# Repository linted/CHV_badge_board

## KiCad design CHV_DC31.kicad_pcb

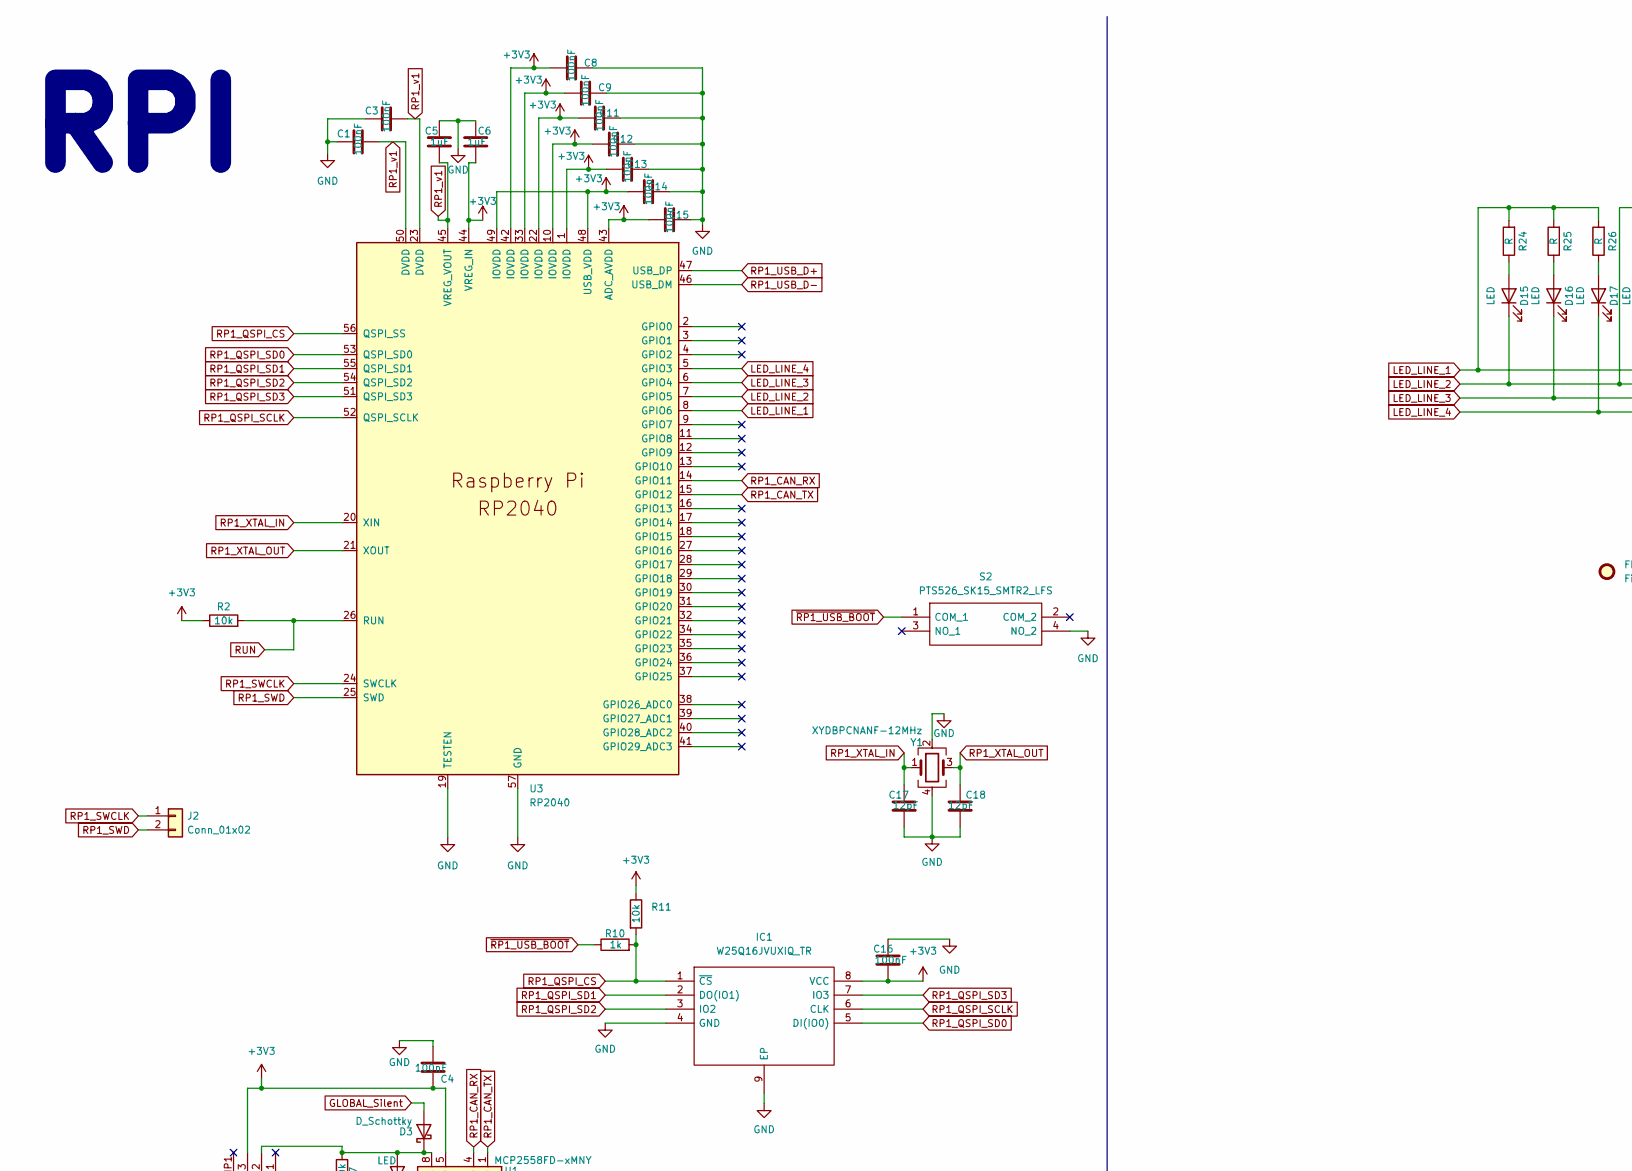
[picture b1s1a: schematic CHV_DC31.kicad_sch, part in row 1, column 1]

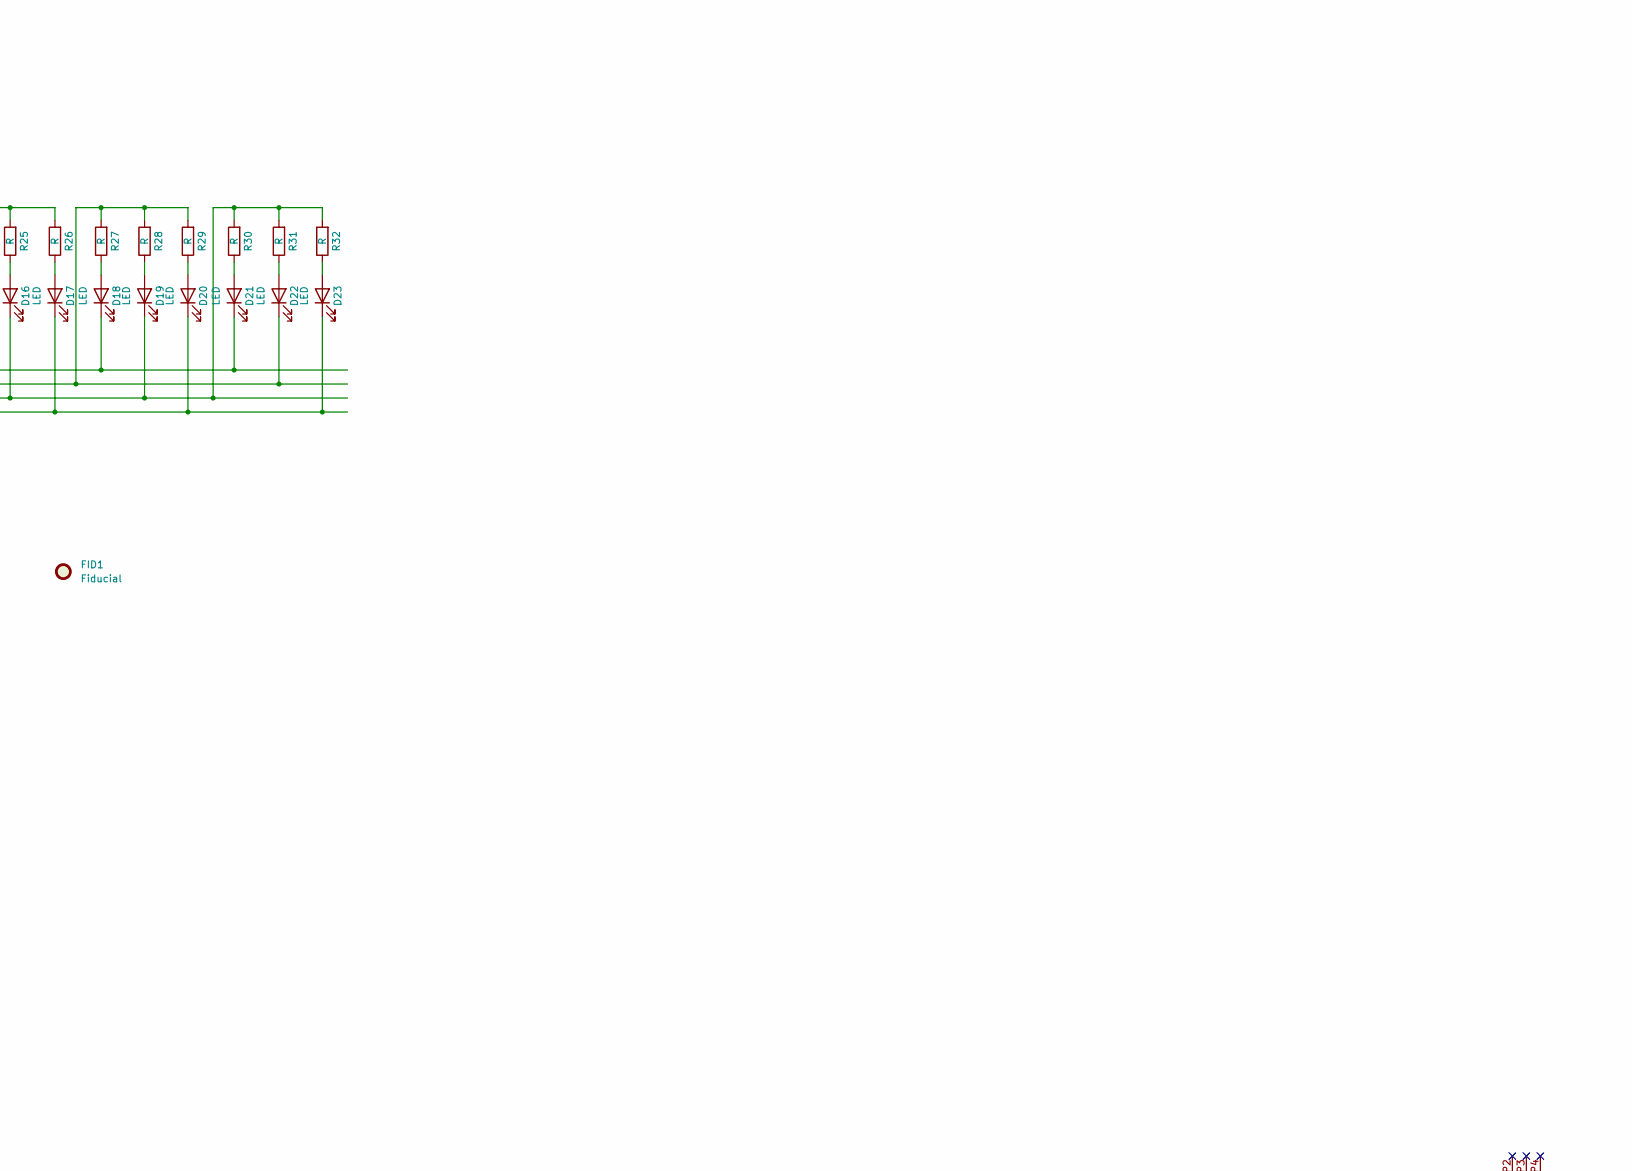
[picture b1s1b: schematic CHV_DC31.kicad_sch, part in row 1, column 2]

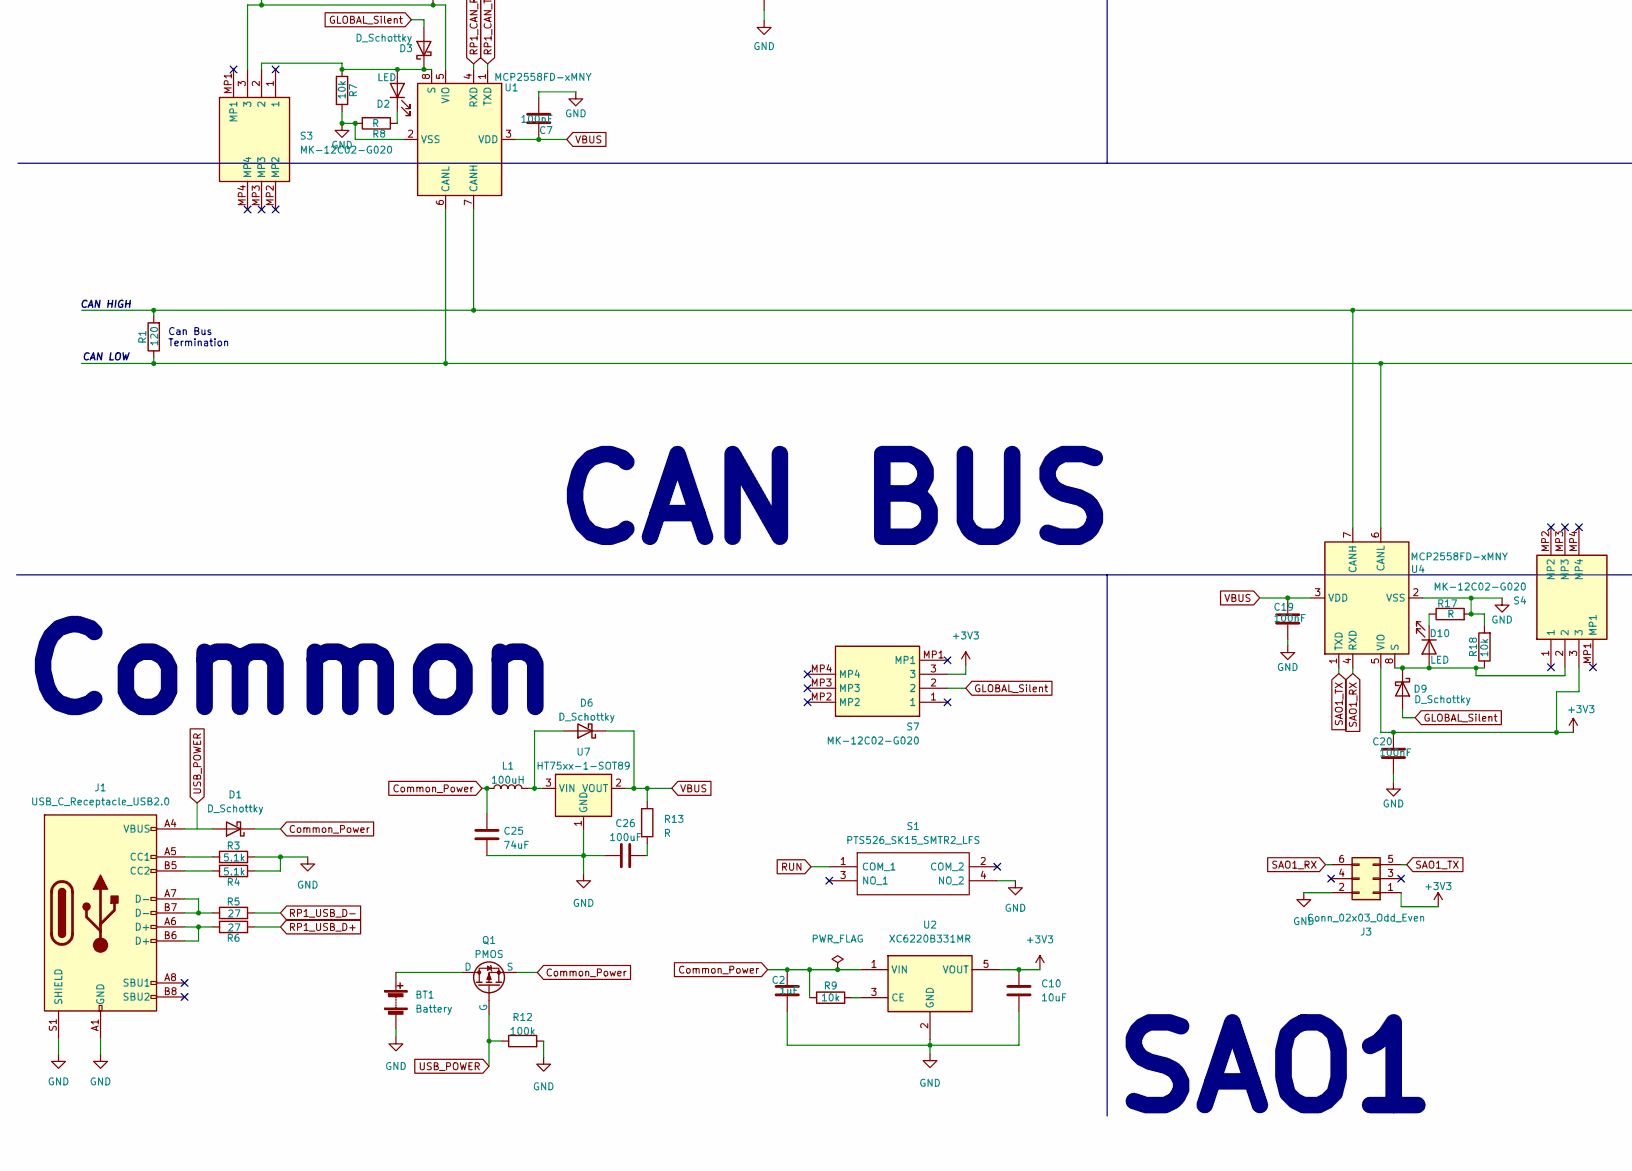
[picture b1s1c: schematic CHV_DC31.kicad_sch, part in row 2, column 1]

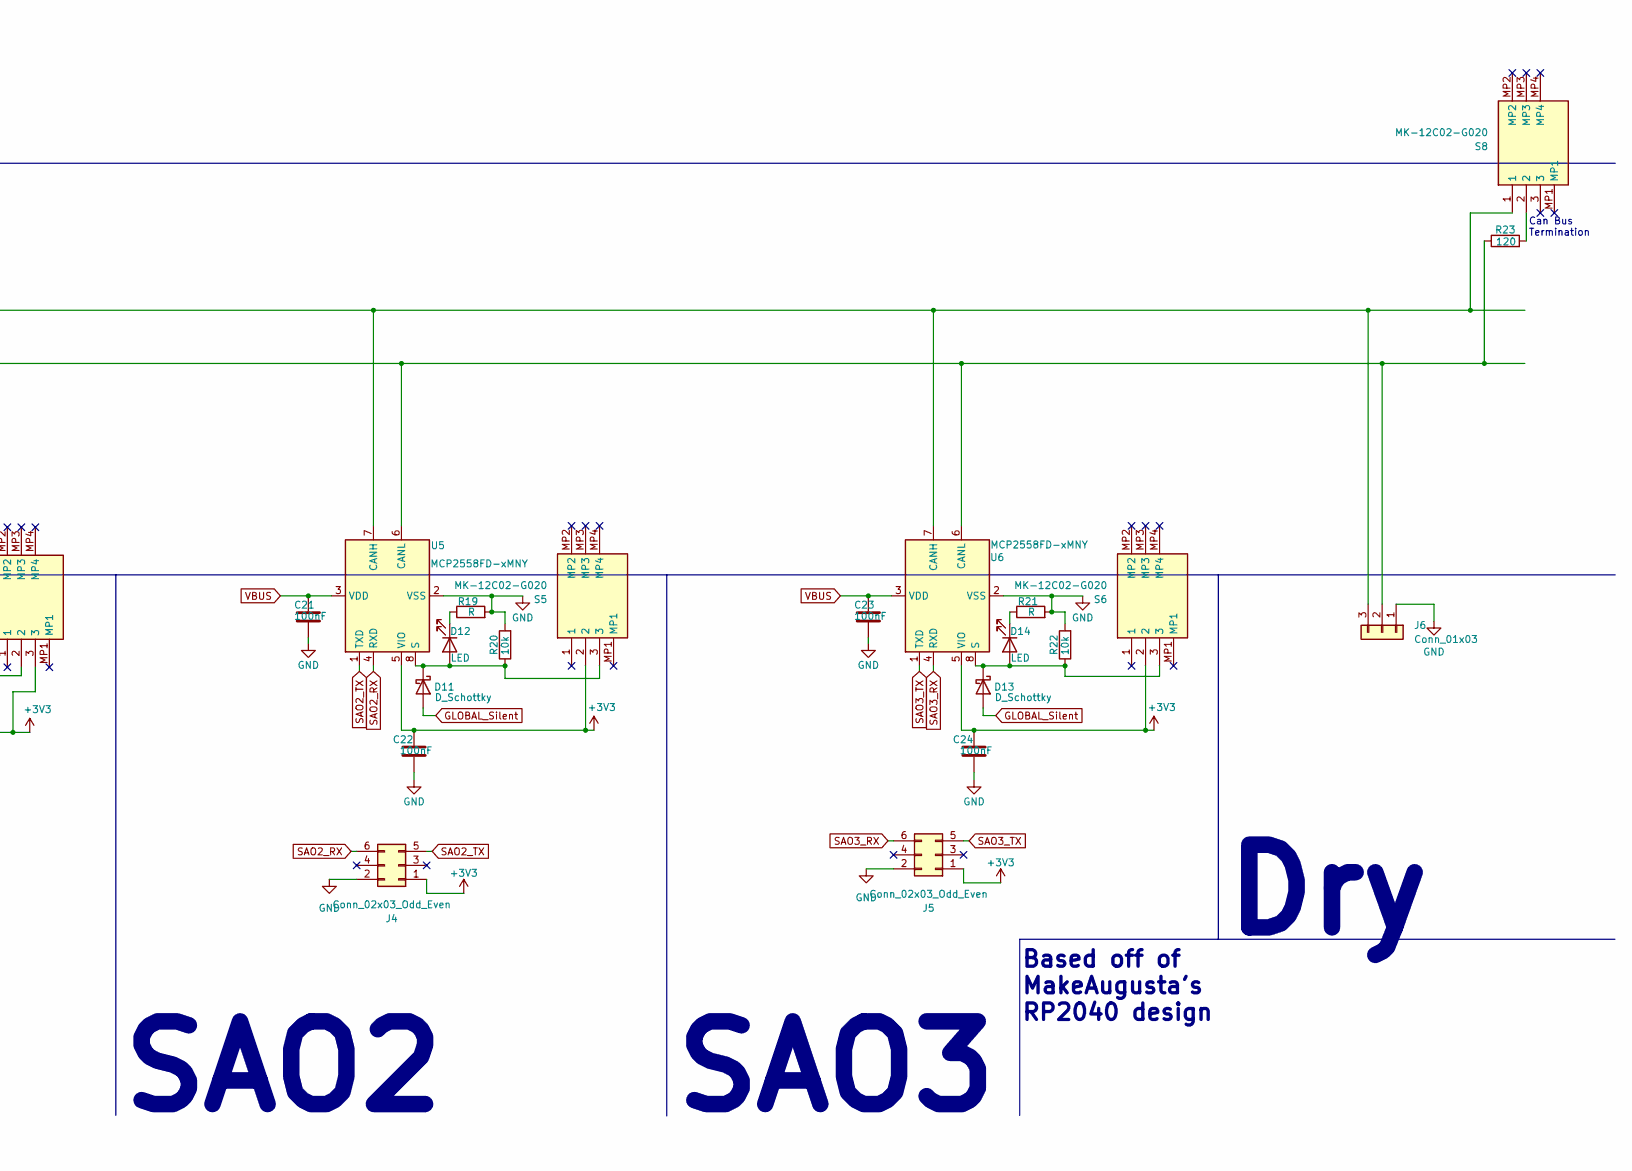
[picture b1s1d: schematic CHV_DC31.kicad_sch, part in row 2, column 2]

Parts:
BT1: Battery; BatteryHolder_Keystone_2462_2xAA
C1, C3, C4, C7, C8, C9, C11, C12, C13, C14, C15, C16, C19, C20, C21, C22, C23, C24: 100nF; C_0805_2012Metric
C2, C5, C6: 1uF; C_0805_2012Metric
C10: 10uF; C_0805_2012Metric
C17, C18: 12pF; C_0805_2012Metric
C25: 74uF; C_0805_2012Metric
C26: 100uF; C_0805_2012Metric
D1, D3, D6, D9, D11, D13: D_Schottky; D_SOD-123
D2, D10, D12, D14: LED; LED_1206_3216Metric
D15, D16, D17, D18, D19, D20, D21, D22, D23: LED; P2-1206RTCS2-0.9T-F
FID1: Fiducial; engine_DC31
IC1: W25Q16JVUXIQ_TR; SON50P300X200X60-9N; Manufacturer_Part_Number W25Q16JVUXIQ TR
J1: USB_C_Receptacle_USB2.0; USB_C_Receptacle_HRO_TYPE-C-31-M-12
J2: Conn_01x02; SolderJumper-2_P1.3mm_Open_Pad1.0x1.5mm
J3, J4, J5: Conn_02x03_Odd_Even; Badgelife-SAOv169-BADGE-2x3
J6: Conn_01x03; PinHeader_1x03_P2.54mm_Vertical
L1: 100uH; L_0805_2012Metric
Q1: PMOS; SOT-23
R1, R23: 120; R_0805_2012Metric
R2, R7, R9, R11, R18, R20, R22: 10k; R_0805_2012Metric
R3, R4: 5.1k; R_0805_2012Metric
R5, R6: 27; R_0805_2012Metric
R8, R13, R17, R19, R21, R24, R25, R26, R27, R28, R29, R30, R31, R32: R; R_0805_2012Metric
R10: 1k; R_0805_2012Metric
R12: 100k; R_0805_2012Metric
S1, S2: PTS526_SK15_SMTR2_LFS; PTS526SK15SMTR2LFS; Manufacturer_Part_Number PTS526 SK15 SMTR2 LFS
S3, S4, S5, S6, S7, S8: MK-12C02-G020; MK12C02G020; Manufacturer_Part_Number MK-12C02-G020
U1, U4, U5, U6: MCP2558FD-xMNY; TDFN-8-1EP_3x2mm_P0.5mm_EP1.80x1.65mm
U2: XC6220B331MR; SOT-23-5
U3: RP2040; RP2040-QFN-56
U7: HT75xx-1-SOT89; SOT-89-3
Y1: XYDBPCNANF-12MHz; Crystal_XYDBPCNANF-12MHZ

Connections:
+3V3: C4.1, C6.2, C8.1, C9.1, C10.1, C11.1, C12.1, C13.1, C14.1, C15.1, C16.2, C20.1, C22.1, C24.1, IC1.8 (VCC), J3.1, J4.1, J5.1, R2.1, R11.1, S3.3, S4.3, S5.2, S6.2, S7.3, U1.5 (VIO), U2.5 (VOUT), U3.1 (IOVDD), U3.10 (IOVDD), U3.22 (IOVDD), U3.33 (IOVDD), U3.42 (IOVDD), U3.43 (ADC_AVDD), U3.44 (VREG_IN), U3.48 (USB_VDD), U3.49 (IOVDD), U4.5 (VIO), U5.5 (VIO), U6.5 (VIO)
Common_Power: C2.1, C25.1, D1.1 (K), L1.1, Q1.3 (S), R9.1, U2.1 (VIN)
GLOBAL_Silent: D3.2 (A), D9.2 (A), D11.2 (A), D13.2 (A), S7.2
GND: BT1.2 (-), C1.1, C2.2, C3.1, C4.2, C5.1, C6.1, C7.2, C8.2, C9.2, C10.2, C11.2, C12.2, C13.2, C14.2, C15.2, C16.1, C17.2, C18.2, C19.2, C20.2, C21.2, C22.2, C23.2, C24.2, C25.2, C26.1, IC1.4 (GND), IC1.9 (EP), J1.A1 (GND), J1.A12 (GND), J1.B1 (GND), J1.B12 (GND), J1.S1 (SHIELD), J3.2, J4.2, J5.2, J6.1, R3.2, R4.2, R7.2, R8.2, R12.2, R17.2, R18.2, R19.2, R20.2, R21.2, R22.2, S1.4 (NO_2), S2.4 (NO_2), U1.2 (VSS), U1.9 (VSS), U2.2 (GND), U3.19 (TESTEN), U3.57 (GND), U4.2 (VSS), U4.9 (VSS), U5.2 (VSS), U5.9 (VSS), U6.2 (VSS), U6.9 (VSS), U7.1 (GND), Y1.2, Y1.4
LED_LINE_1: D18.1 (K), D21.1 (K), R24.2, R25.2, R26.2, U3.8 (GPIO6)
LED_LINE_2: D15.1 (K), D22.1 (K), R27.2, R28.2, R29.2, U3.7 (GPIO5)
LED_LINE_3: D16.1 (K), D19.1 (K), R30.2, R31.2, R32.2, U3.6 (GPIO4)
LED_LINE_4: D17.1 (K), D20.1 (K), D23.1 (K), U3.5 (GPIO3)
unnamed: BT1.1 (+), Q1.1 (D)
unnamed: C26.2, R13.2
unnamed: D1.2 (A), J1.A4 (VBUS), J1.A9 (VBUS), J1.B4 (VBUS), J1.B9 (VBUS)
unnamed: D2.2 (A), D3.1 (K), R7.1, S3.2, U1.8 (S)
unnamed: D2.1 (K), R8.1
unnamed: D6.2 (A), L1.2, U7.3 (VIN)
unnamed: D9.1 (K), D10.2 (A), R18.1, S4.2, U4.8 (S)
unnamed: D10.1 (K), R17.1
unnamed: D11.1 (K), D12.2 (A), R20.1, S5.3, U5.8 (S)
unnamed: D12.1 (K), R19.1
unnamed: D13.1 (K), D14.2 (A), R22.1, S6.3, U6.8 (S)
unnamed: D14.1 (K), R21.1
unnamed: D15.2 (A), R24.1
unnamed: D16.2 (A), R25.1
unnamed: D17.2 (A), R26.1
unnamed: D18.2 (A), R27.1
unnamed: D19.2 (A), R28.1
unnamed: D20.2 (A), R29.1
unnamed: D21.2 (A), R30.1
unnamed: D22.2 (A), R31.1
unnamed: D23.2 (A), R32.1
unnamed: J1.A5 (CC1), R3.1
unnamed: J1.B5 (CC2), R4.1
unnamed: J1.A6 (D+), J1.B6 (D+), R6.1
unnamed: J1.A7 (D-), J1.B7 (D-), R5.1
unnamed: J6.2, R1.1, R23.1, U1.6 (CANL), U4.6 (CANL), U5.6 (CANL), U6.6 (CANL)
unnamed: J6.3, R1.2, S8.1, U1.7 (CANH), U4.7 (CANH), U5.7 (CANH), U6.7 (CANH)
unnamed: R23.2, S8.2
unnamed: R9.2, U2.3 (CE)
RP1_CAN_RX: U1.4 (RXD), U3.14 (GPIO11)
RP1_CAN_TX: U1.1 (TXD), U3.15 (GPIO12)
RP1_QSPI_CS: IC1.1 (~CS), R10.2, R11.2, U3.56 (QSPI_SS)
RP1_QSPI_SCLK: IC1.6 (CLK), U3.52 (QSPI_SCLK)
RP1_QSPI_SD0: IC1.5 (DI(IO0)), U3.53 (QSPI_SD0)
RP1_QSPI_SD1: IC1.2 (DO(IO1)), U3.55 (QSPI_SD1)
RP1_QSPI_SD2: IC1.3 (IO2), U3.54 (QSPI_SD2)
RP1_QSPI_SD3: IC1.7 (IO3), U3.51 (QSPI_SD3)
RP1_SWCLK: J2.1, U3.24 (SWCLK)
RP1_SWD: J2.2, U3.25 (SWD)
RP1_USB_D+: R6.2, U3.47 (USB_DP)
RP1_USB_D-: R5.2, U3.46 (USB_DM)
RP1_XTAL_IN: C17.1, U3.20 (XIN), Y1.1
RP1_XTAL_OUT: C18.1, U3.21 (XOUT), Y1.3
RP1_v1: C1.2, C3.2, C5.2, U3.23 (DVDD), U3.45 (VREG_VOUT), U3.50 (DVDD)
RUN: R2.2, S1.1 (COM_1), U3.26 (RUN)
SAO1_RX: J3.6, U4.4 (RXD)
SAO1_TX: J3.5, U4.1 (TXD)
SAO2_RX: J4.6, U5.4 (RXD)
SAO2_TX: J4.5, U5.1 (TXD)
SAO3_RX: J5.6, U6.4 (RXD)
SAO3_TX: J5.5, U6.1 (TXD)
USB_POWER: Q1.2 (G), R12.1
VBUS: C7.1, C19.1, C21.1, C23.1, D6.1 (K), R13.1, U1.3 (VDD), U4.3 (VDD), U5.3 (VDD), U6.3 (VDD), U7.2 (VOUT)
~RP1_USB_BOOT: R10.1, S2.1 (COM_1)

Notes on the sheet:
Based off of MakeAugusta's RP2040 design
Dry
SAO2
Can Bus Termination
CAN HIGH
SAO3
CAN BUS
CAN LOW
Common
RPI
SAO1

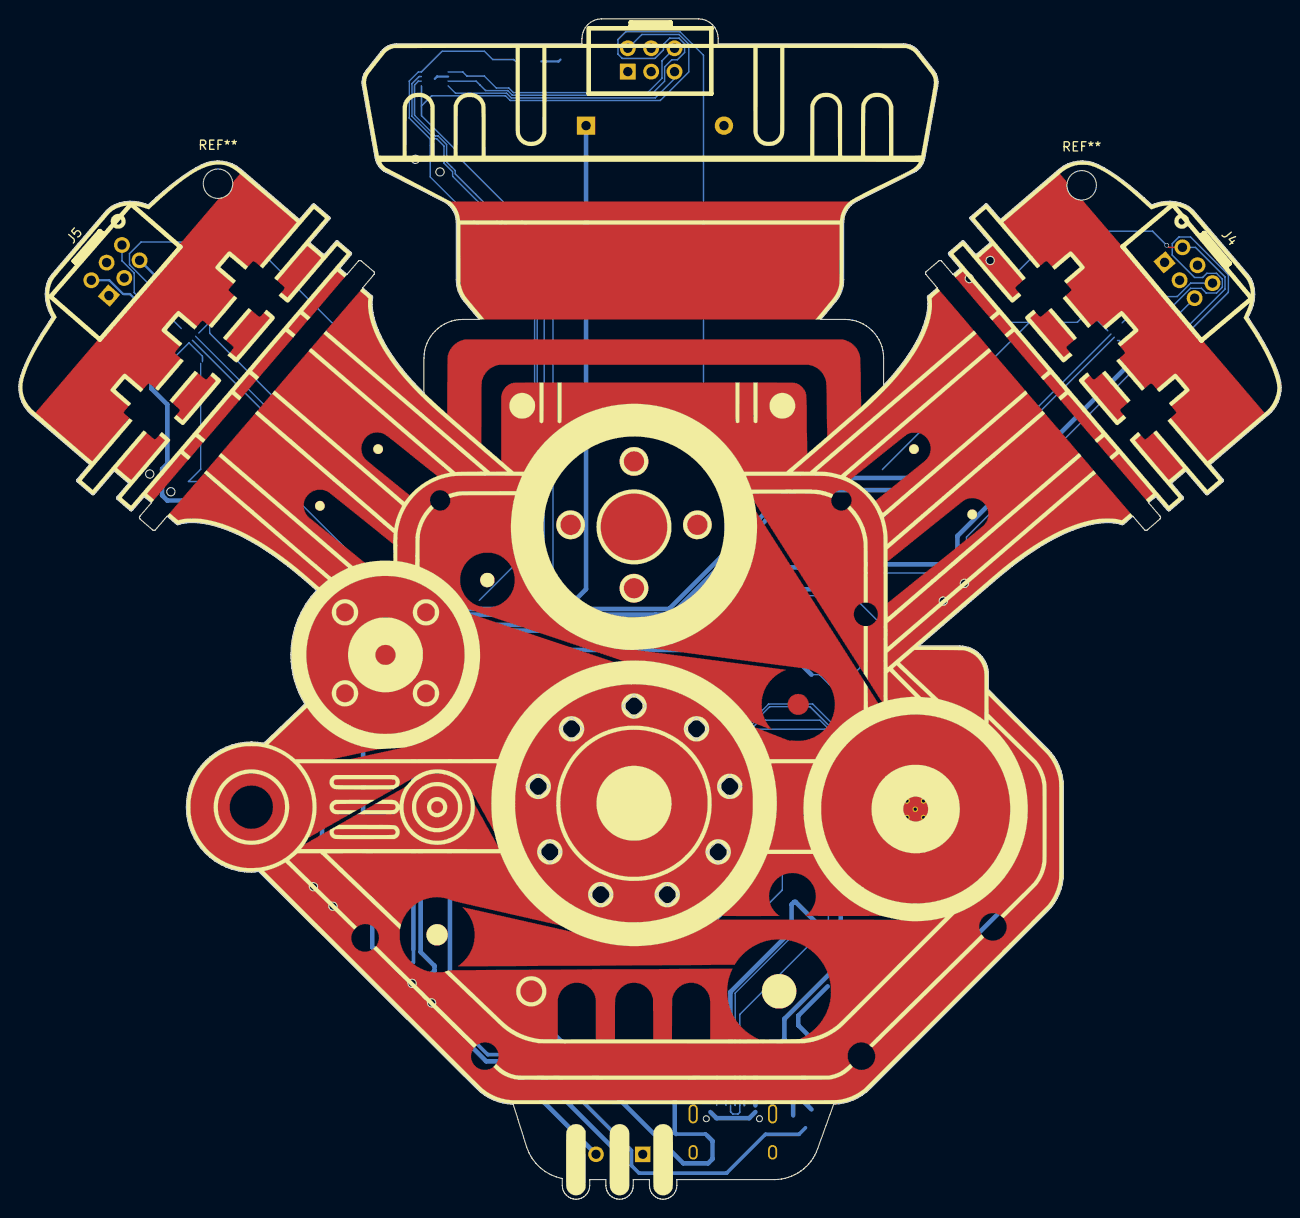
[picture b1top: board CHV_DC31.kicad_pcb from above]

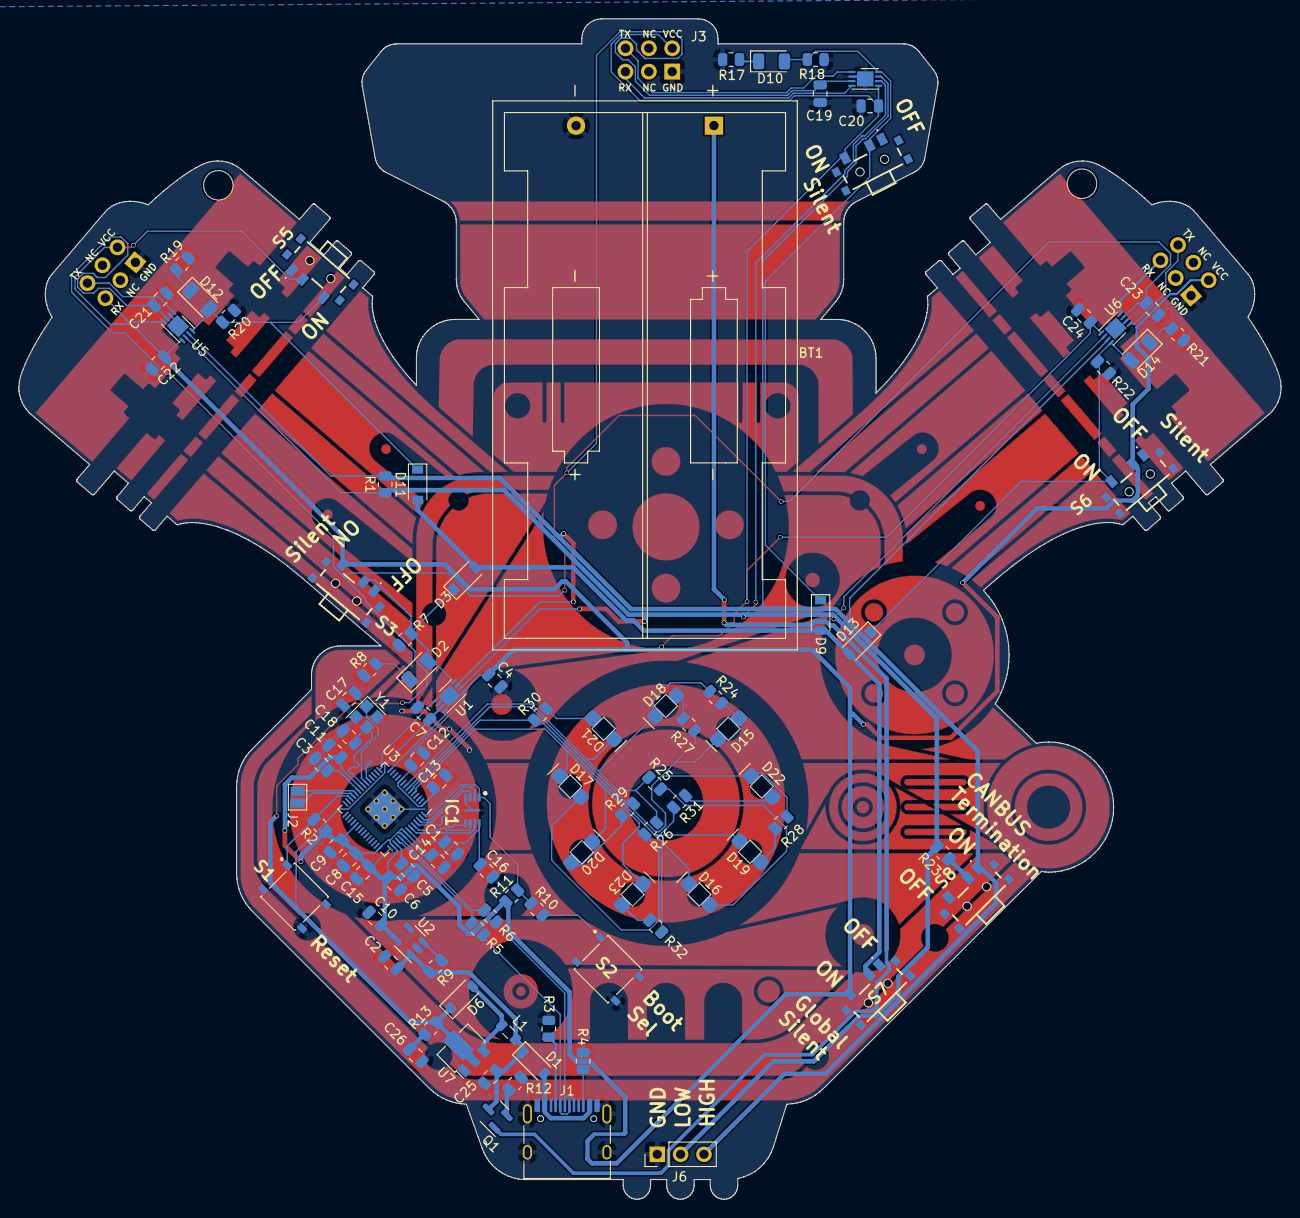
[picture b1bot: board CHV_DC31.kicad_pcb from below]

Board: 2 copper layers, 137.3 x 128.3 mm, 101 parts (97 on the bottom side), 62 nets.

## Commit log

2022-12-20 added devboard layout and schematic
2023-02-02 started work on final art
2023-02-04 getting close to finishing
2023-02-11 final version of prototype1 art
2023-04-02 starting on new simpler desing
2023-04-08 layed out led ring
2023-04-09 power
2023-04-14 closer, but also further
2023-04-15 more updates
2023-04-16 sooooooo close
2023-04-19 getting closer
2023-04-22 more changes
2023-04-22 almost done!
2023-04-24 HOLY COW IT'S DONE
2023-04-26 We are SOOOOO close
2023-04-29 Finished DRC!
2023-04-29 added countersink leds
2023-05-03 finished
2023-05-04 LGTM SHIP IT
2023-05-22 Holy cow, done
2023-06-05 forgot to post this
